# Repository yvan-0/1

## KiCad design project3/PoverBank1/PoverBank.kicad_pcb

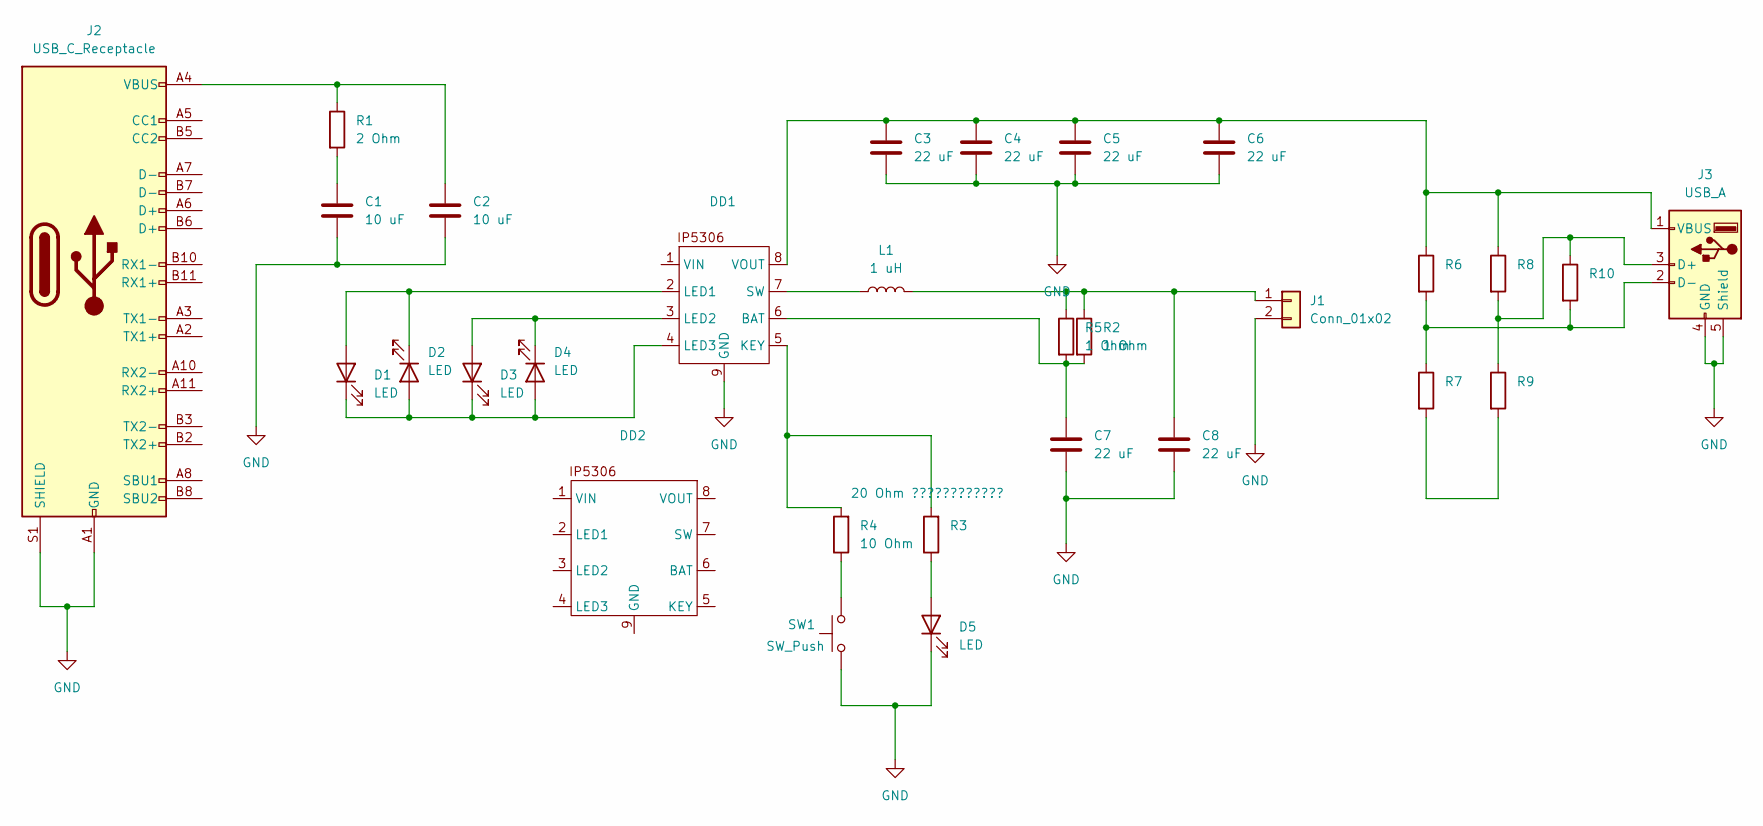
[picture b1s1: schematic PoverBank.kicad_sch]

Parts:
C1, C2: 10 uF; C_1206_3216Metric_Pad1.33x1.80mm_HandSolder
C3, C4, C5, C6, C7, C8: 22 uF; C_1206_3216Metric_Pad1.33x1.80mm_HandSolder
D1, D2, D3, D4: LED; LED_0603_1608Metric_Pad1.05x0.95mm_HandSolder
D5: LED; LED_D5.0mm_IRBlack
DD1: SOIC-8-1EP_3.9x4.9mm_P1.27mm_EP2.95x4.9mm_Mask2.71x3.4mm_Th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
DD2: (no value)
J1: Conn_01x02; JST_XH_B2B-XH-A_1x02_P2.50mm_Vertical
J2: USB_C_Receptacle; USB_C_Receptacle_JAE_DX07S024WJ3R400
J3: USB_A; USB_A_CONNFLY_DS1095-WNR0
L1: 1 uH; L_6.3x6.3_H3
R1: 2 Ohm; R_0603_1608Metric_Pad0.98x0.95mm_HandSolder
R2, R5: 1 Ohm; R_0603_1608Metric_Pad0.98x0.95mm_HandSolder
R3: 20 Ohm ????????????; R_0603_1608Metric_Pad0.98x0.95mm_HandSolder
R4: 10 Ohm; R_0603_1608Metric_Pad0.98x0.95mm_HandSolder
R6, R7, R8, R9, R10: R_0603_1608Metric_Pad0.98x0.95mm_HandSolder
SW1: SW_Push; SW_PUSH_6mm_H13mm

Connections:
GND: C1.2, C2.2, C3.2, C4.2, C5.2, C6.2, C7.2, C8.2, D5.1 (K), DD1.9 (GND), J1.2, J2.A1 (GND), J2.A12 (GND), J2.B1 (GND), J2.B12 (GND), J2.S1 (SHIELD), J3.4 (GND), J3.5 (Shield), SW1.1
unnamed: C1.1, R1.2
unnamed: C2.1, J2.A4 (VBUS), J2.A9 (VBUS), J2.B4 (VBUS), J2.B9 (VBUS), R1.1
unnamed: D1.2 (A), D2.1 (K), DD1.2 (LED1)
unnamed: D1.1 (K), D2.2 (A), D3.1 (K), D4.2 (A), DD1.4 (LED3)
unnamed: D3.2 (A), D4.1 (K), DD1.3 (LED2)
unnamed: D5.2 (A), R3.1
unnamed: C7.1, DD1.6 (BAT), R2.2, R5.2
unnamed: DD1.5 (KEY), R3.2, R4.2
unnamed: DD1.7 (SW), L1.1
unnamed: C3.1, C4.1, C5.1, C6.1, DD1.8 (VOUT), J3.1 (VBUS), R6.1, R8.1
unnamed: C8.1, J1.1, L1.2, R2.1, R5.1
unnamed: J3.3 (D+), R8.2, R9.1, R10.1
unnamed: J3.2 (D-), R6.2, R7.1, R10.2
unnamed: R4.1, SW1.2
unnamed: R7.2, R9.2

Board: 2 copper layers, 29 parts (0 on the bottom side), 16 nets, no tracks yet.

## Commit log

2024-12-02 added main file v.3
